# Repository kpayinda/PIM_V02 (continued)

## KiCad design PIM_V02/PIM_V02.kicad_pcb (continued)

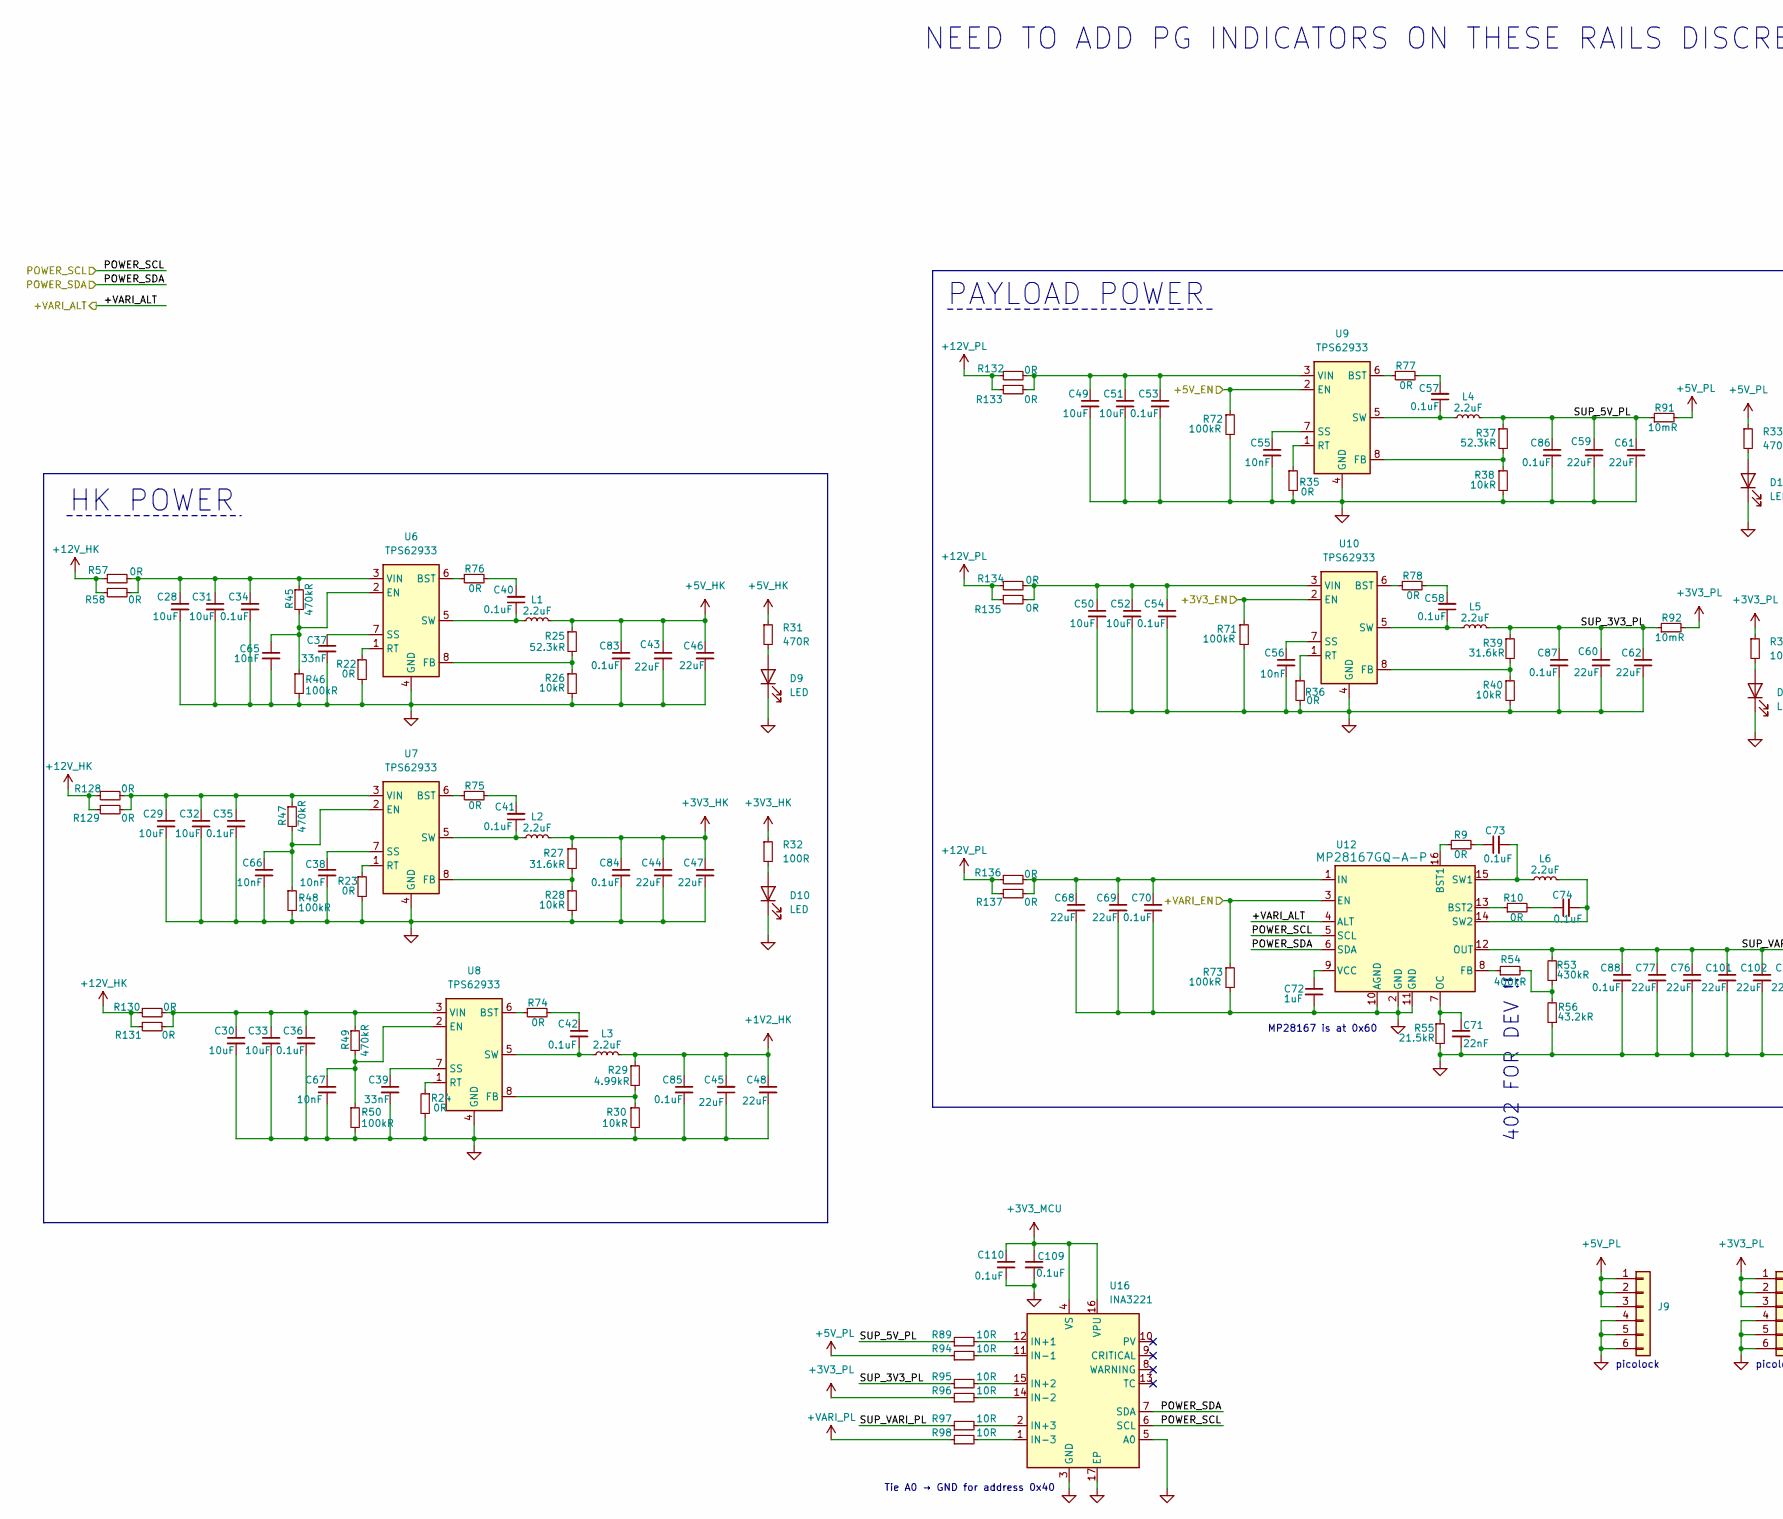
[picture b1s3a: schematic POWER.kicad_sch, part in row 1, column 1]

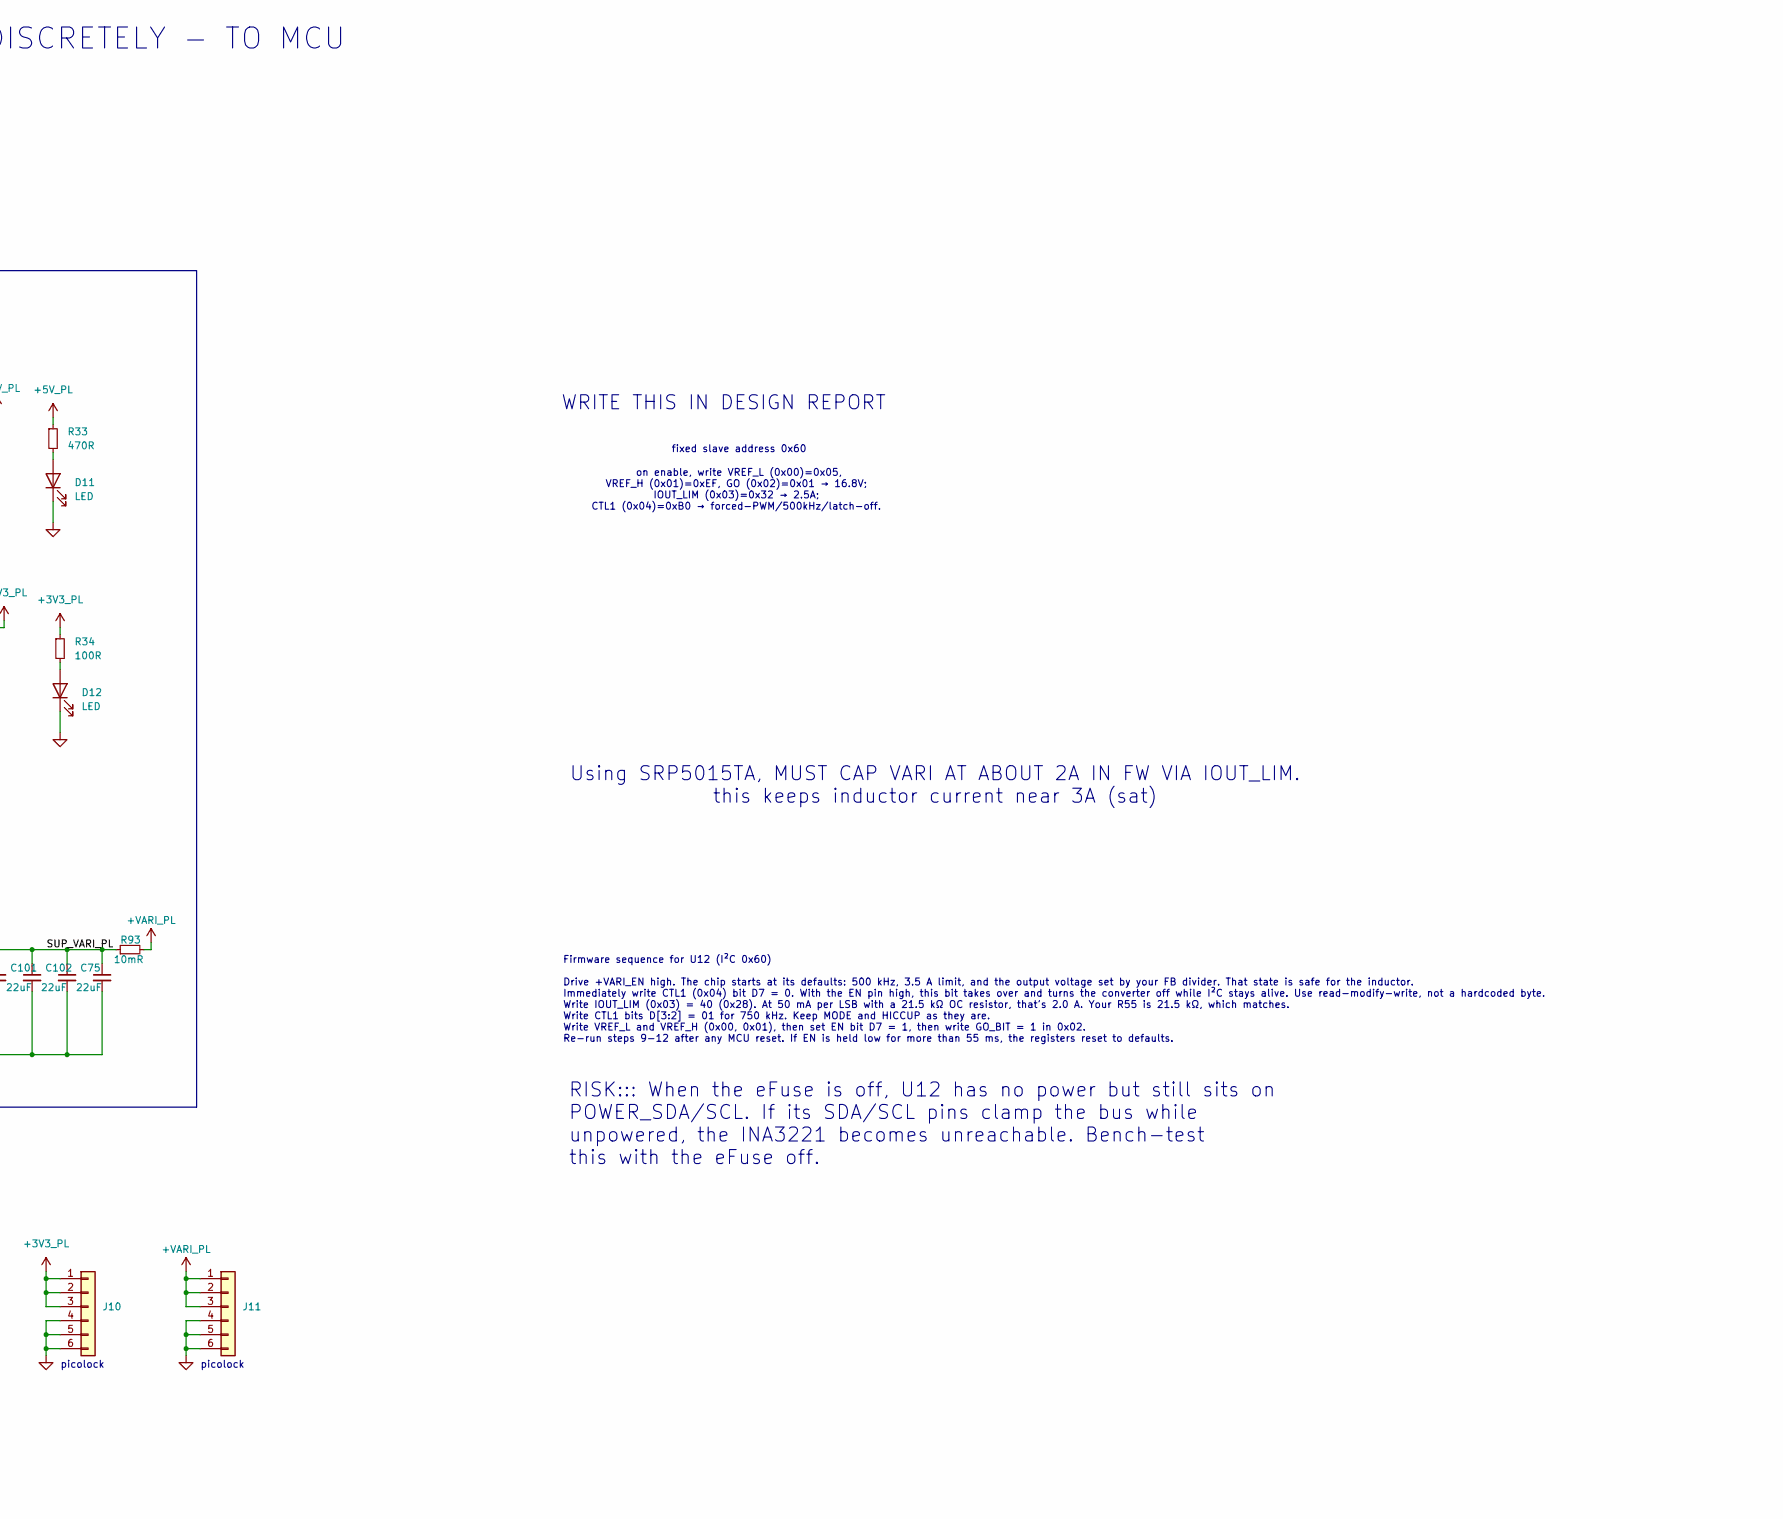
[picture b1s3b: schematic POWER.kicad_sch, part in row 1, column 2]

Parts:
C28, C29, C30, C31, C32, C33, C49, C50, C51, C52: 10uF; C_0603_1608Metric; MPN GRT188R61E106ME13D
C34, C35, C36, C40, C41, C42, C53, C54, C57, C58, C70, C73, C74, C83, C84, C85, C86, C87, C88, C109, C110: 0.1uF; C_0603_1608Metric; MPN GCM188R71H104KA57D
C37, C39: 33nF; C_0603_1608Metric; MPN AC0603KRX7R9BB333
C38, C55, C56, C65, C66, C67: 10nF; C_0603_1608Metric; MPN GCM188R71H103KA37J
C43, C44, C45, C46, C47, C48, C59, C60, C61, C62: 22uF; C_0603_1608Metric; MPN GRT188R61A226ME13D
C68, C69, C75, C76, C77, C101, C102: 22uF; C_0805_2012Metric; MPN GRM21BR61E226ME44L
C71: 22nF; C_0603_1608Metric; MPN GCM188R71H223KA37J
C72: 1uF; C_0603_1608Metric; MPN GCM188R71E105KA64J
D9, D10, D11, D12: LED; LED_0603_1608Metric; MPN 150060GS75000
J9, J10, J11: Conn_01x06; Molex_Pico-Lock_504050-0691_1x06-1MP_P1.50mm_Horizontal; MPN 5040500691
L1, L2, L3, L4, L5, L6: 2.2uF; SRP5015TA-2R2M; MPN SRP5015TA-2R2M
R9, R10, R22, R23, R24, R35, R36, R57, R58, R74, R75, R76, R77, R78, R128, R129, R130, R131, R132, R133, R134, R135, R136, R137: 0R; R_0603_1608Metric; MPN ERJ-3GEY0R00V
R25, R37: 52.3kR; R_0603_1608Metric; MPN ERJ-3EKF5232V
R26, R28, R30, R38, R40: 10kR; R_0603_1608Metric; MPN ERJ-3EKF1002V
R27, R39: 31.6kR; R_0603_1608Metric; MPN ERJ-3EKF3162V
R29: 4.99kR; R_0603_1608Metric; MPN ERJ-3EKF4991V
R31, R33: 470R; R_0603_1608Metric; MPN ERJ-3EKF4700V
R32, R34: 100R; R_0603_1608Metric; MPN ERJ-3EKF1000V
R45, R47, R49: 470kR; R_0603_1608Metric; MPN ERJ-3EKF4703V
R46, R48, R50, R71, R72, R73: 100kR; R_0603_1608Metric; MPN ERJ-3EKF1003V
R53: 430kR; R_0603_1608Metric; MPN ERJ-3EKF4303V
R54: 400kR; R_0603_1608Metric; MPN ERJ-3EKF4023V
R55: 21.5kR; R_0603_1608Metric; MPN ERJ-3EKF2152V
R56: 43.2kR; R_0603_1608Metric; MPN ERJ-3EKF4322V
R89, R94, R95, R96, R97, R98: 10R; R_0603_1608Metric
R91, R92, R93: 10mR; R_0603_1608Metric; MPN WSLP2512R0100DEA
U6, U7, U8, U9, U10: TPS62933; SOT-583-8; MPN TPS62933DRLR
U12: MP28167GQ-A-P; MPN MP28167GQ-A-P
U16: INA3221; Texas_RGV0016A_VQFN-16-1EP_4x4mm_P0.65mm_EP2.1x2.1mm

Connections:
+1V2_HK: C45.2, C48.1, C85.1, L3.2, R29.1; also elsewhere on the board
+3V3_HK: C44.1, C47.1, C84.1, L2.2, R27.1, R32.1; also elsewhere on the board
+3V3_MCU: C109.1, C110.1, U16.4 (VS), U16.16 (VPU); also elsewhere on the board
+3V3_PL: J10.1, J10.2, J10.3, R34.1, R92.2, R96.1
+5V_HK: C43.1, C46.1, C83.1, L1.2, R25.1, R31.1; also elsewhere on the board
+5V_PL: J9.1, J9.2, J9.3, R33.1, R91.2, R94.1
+12V_HK: R57.1, R58.1, R128.1, R129.1, R130.1, R131.1; also elsewhere on the board
+12V_PL: R132.1, R133.1, R134.1, R135.1, R136.1, R137.1; also elsewhere on the board
+VARI_PL: J11.1, J11.2, J11.3, R93.2, R98.1
/+3V3_EN: R71.1, U10.2 (EN); also elsewhere on the board
/+5V_EN: R72.1, U9.2 (EN); also elsewhere on the board
/+VARI_ALT: U12.4 (ALT); also elsewhere on the board
/+VARI_EN: R73.1, U12.3 (EN); also elsewhere on the board
/POWER/SUP_3V3_PL: C60.1, C62.1, C87.1, L5.2, R39.1, R92.1, R95.1
/POWER/SUP_5V_PL: C59.1, C61.1, C86.1, L4.2, R37.1, R89.1, R91.1
/POWER/SUP_VARI_PL: C75.1, C76.1, C77.1, C88.1, C101.1, C102.1, R53.2, R93.1, R97.1, U12.12 (OUT)
/POWER_SCL: U12.5 (SCL), U16.6 (SCL); also elsewhere on the board
/POWER_SDA: U12.6 (SDA), U16.7 (SDA); also elsewhere on the board
GND: C28.2, C29.2, C30.2, C31.2, C32.2, C33.2, C34.2, C35.2, C36.2, C37.2, C38.2, C39.2, C43.2, C44.2, C45.1, C46.2, C47.2, C48.2, C49.2, C50.2, C51.2, C52.2, C53.2, C54.2, C55.2, C56.2, C59.2, C60.2, C61.2, C62.2, C65.2, C66.2, C67.2, C68.2, C69.2, C70.2, C71.2, C72.2, C75.2, C76.2, C77.2, C83.2, C84.2, C85.2, C86.2, C87.2, C88.2, C101.2, C102.2, C109.2, C110.2, D9.1 (K), D10.1 (K), D11.1 (K), D12.1 (K), J9.4, J9.5, J9.6, J10.4, J10.5, J10.6, J11.4, J11.5, J11.6, R22.2, R23.2, R24.2, R26.2, R28.2, R30.2, R35.2, R36.2, R38.2, R40.2, R46.2, R48.2, R50.2, R55.2, R56.1, R71.2, R72.2, R73.2, U6.4 (GND), U7.4 (GND), U8.4 (GND), U9.4 (GND), U10.4 (GND), U12.2 (GND), U12.10 (AGND), U12.11 (GND), U16.3 (GND), U16.5 (A0), U16.17 (EP); also elsewhere on the board
unnamed: C40.2, R76.2
unnamed: C41.2, R75.2
unnamed: C42.1, R74.2
unnamed: C57.2, R77.2
unnamed: C58.2, R78.2
unnamed: C73.1, R9.2
unnamed: C74.1, R10.2
unnamed: D9.2 (A), R31.2
unnamed: D10.2 (A), R32.2
unnamed: D11.2 (A), R33.2
unnamed: D12.2 (A), R34.2
unnamed: R53.1, R54.2, R56.2
unnamed: R76.1, U6.6 (BST)
unnamed: C65.1, R45.2, R46.1, U6.2 (EN)
unnamed: R25.2, R26.1, U6.8 (FB)
unnamed: R22.1, U6.1 (RT)
unnamed: C37.1, U6.7 (SS)
unnamed: C40.1, L1.1, U6.5 (SW)
unnamed: C28.1, C31.1, C34.1, R45.1, R57.2, R58.2, U6.3 (VIN)
unnamed: R75.1, U7.6 (BST)
unnamed: C66.1, R47.2, R48.1, U7.2 (EN)
unnamed: R27.2, R28.1, U7.8 (FB)
unnamed: R23.1, U7.1 (RT)
unnamed: C38.1, U7.7 (SS)
unnamed: C41.1, L2.1, U7.5 (SW)
unnamed: C29.1, C32.1, C35.1, R47.1, R128.2, R129.2, U7.3 (VIN)
unnamed: R74.1, U8.6 (BST)
unnamed: C67.1, R49.2, R50.1, U8.2 (EN)
unnamed: R29.2, R30.1, U8.8 (FB)
unnamed: R24.1, U8.1 (RT)
unnamed: C39.1, U8.7 (SS)
unnamed: C42.2, L3.1, U8.5 (SW)
unnamed: C30.1, C33.1, C36.1, R49.1, R130.2, R131.2, U8.3 (VIN)
unnamed: R77.1, U9.6 (BST)
unnamed: R37.2, R38.1, U9.8 (FB)
unnamed: R35.1, U9.1 (RT)
unnamed: C55.1, U9.7 (SS)
unnamed: C57.1, L4.1, U9.5 (SW)
unnamed: C49.1, C51.1, C53.1, R132.2, R133.2, U9.3 (VIN)
unnamed: R78.1, U10.6 (BST)
unnamed: R39.2, R40.1, U10.8 (FB)
unnamed: R36.1, U10.1 (RT)
unnamed: C56.1, U10.7 (SS)
unnamed: C58.1, L5.1, U10.5 (SW)
unnamed: C50.1, C52.1, C54.1, R134.2, R135.2, U10.3 (VIN)
unnamed: R9.1, U12.16 (BST1)
unnamed: R10.1, U12.13 (BST2)
unnamed: R54.1, U12.8 (FB)
unnamed: C68.1, C69.1, C70.1, R136.2, R137.2, U12.1 (IN)
unnamed: C71.1, R55.1, U12.7 (OC)
unnamed: C73.2, L6.1, U12.15 (SW1)
unnamed: C74.2, L6.2, U12.14 (SW2)
unnamed: C72.1, U12.9 (VCC)
unnamed: R89.2, U16.12 (IN+1)
unnamed: R95.2, U16.15 (IN+2)
unnamed: R97.2, U16.2 (IN+3)
unnamed: R94.2, U16.11 (IN-1)
unnamed: R96.2, U16.14 (IN-2)
unnamed: R98.2, U16.1 (IN-3)

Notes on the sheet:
Firmware sequence for U12 (I²C 0x60) Drive +VARI_EN high. The chip starts at its defaults: 500 kHz, 3.5 A limit, and the output voltage set by your FB divider. That state is safe for the inductor. Immediately write CTL1 (0x04) bit D7 = 0. With the EN pin high, this bit takes over and turns the conv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
WRITE THIS IN DESIGN REPORT
HK POWER
Tie A0 → GND for address 0x40
picolock
on enable, write VREF_L (0x00)=0x05, VREF_H (0x01)=0xEF, GO (0x02)=0x01 → 16.8V; IOUT_LIM (0x03)=0x32 → 2.5A; CTL1 (0x04)=0xB0 → forced-PWM/500kHz/latch-off.
PAYLOAD POWER
MP28167 is at 0x60
NEED TO ADD PG INDICATORS ON THESE RAILS DISCRETELY - TO MCU
Using SRP5015TA, MUST CAP VARI AT ABOUT 2A IN FW VIA IOUT_LIM. this keeps inductor current near 3A (sat)
402 FOR DEV !!
fixed slave address 0x60
RISK::: When the eFuse is off, U12 has no power but still sits on POWER_SDA/SCL. If its SDA/SCL pins clamp the bus while unpowered, the INA3221 becomes unreachable. Bench-test this with the eFuse off.

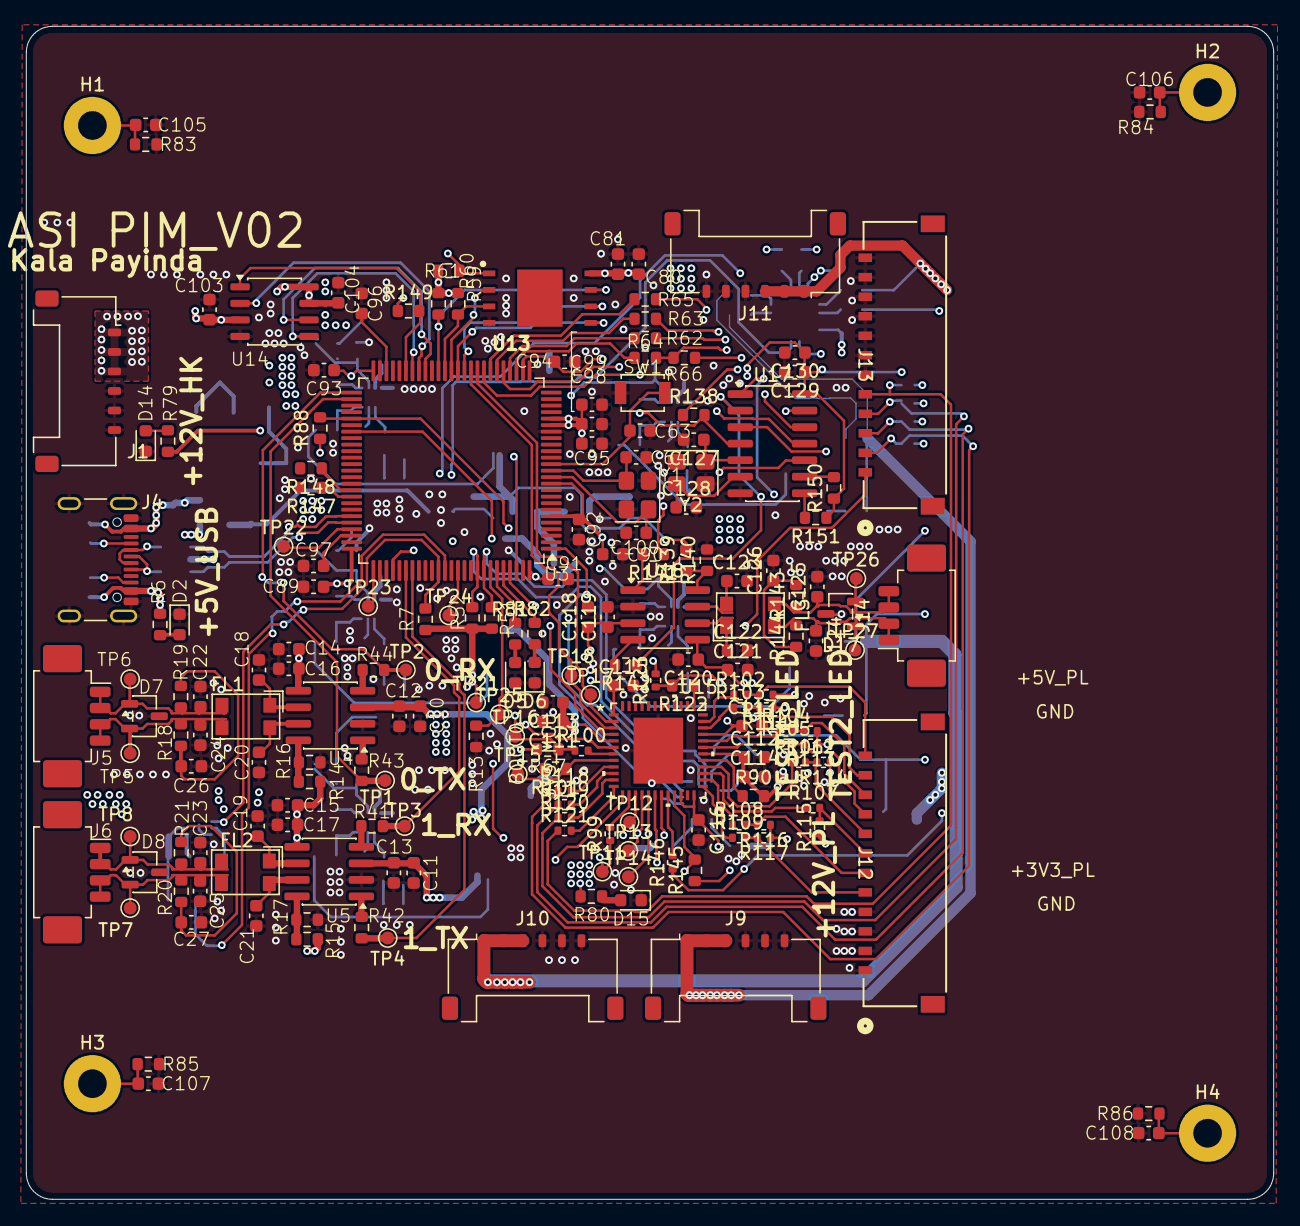
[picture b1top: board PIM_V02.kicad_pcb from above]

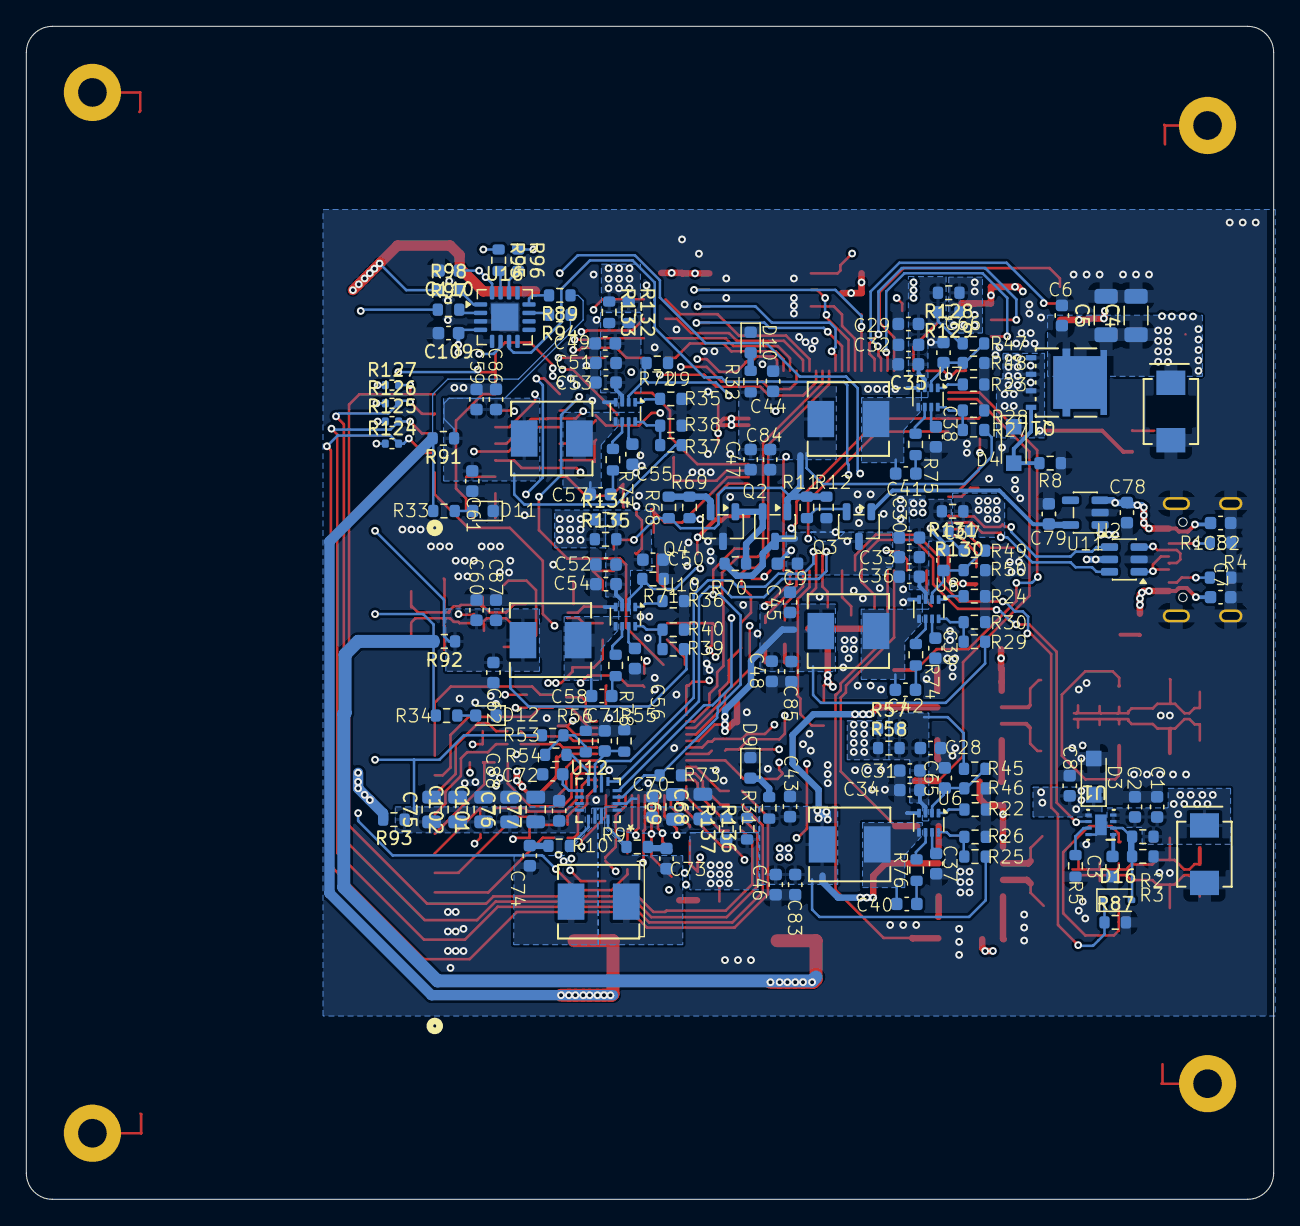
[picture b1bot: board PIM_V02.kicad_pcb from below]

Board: 4 copper layers, 95.9 x 90.2 mm, 369 parts (175 on the bottom side), 211 nets.
